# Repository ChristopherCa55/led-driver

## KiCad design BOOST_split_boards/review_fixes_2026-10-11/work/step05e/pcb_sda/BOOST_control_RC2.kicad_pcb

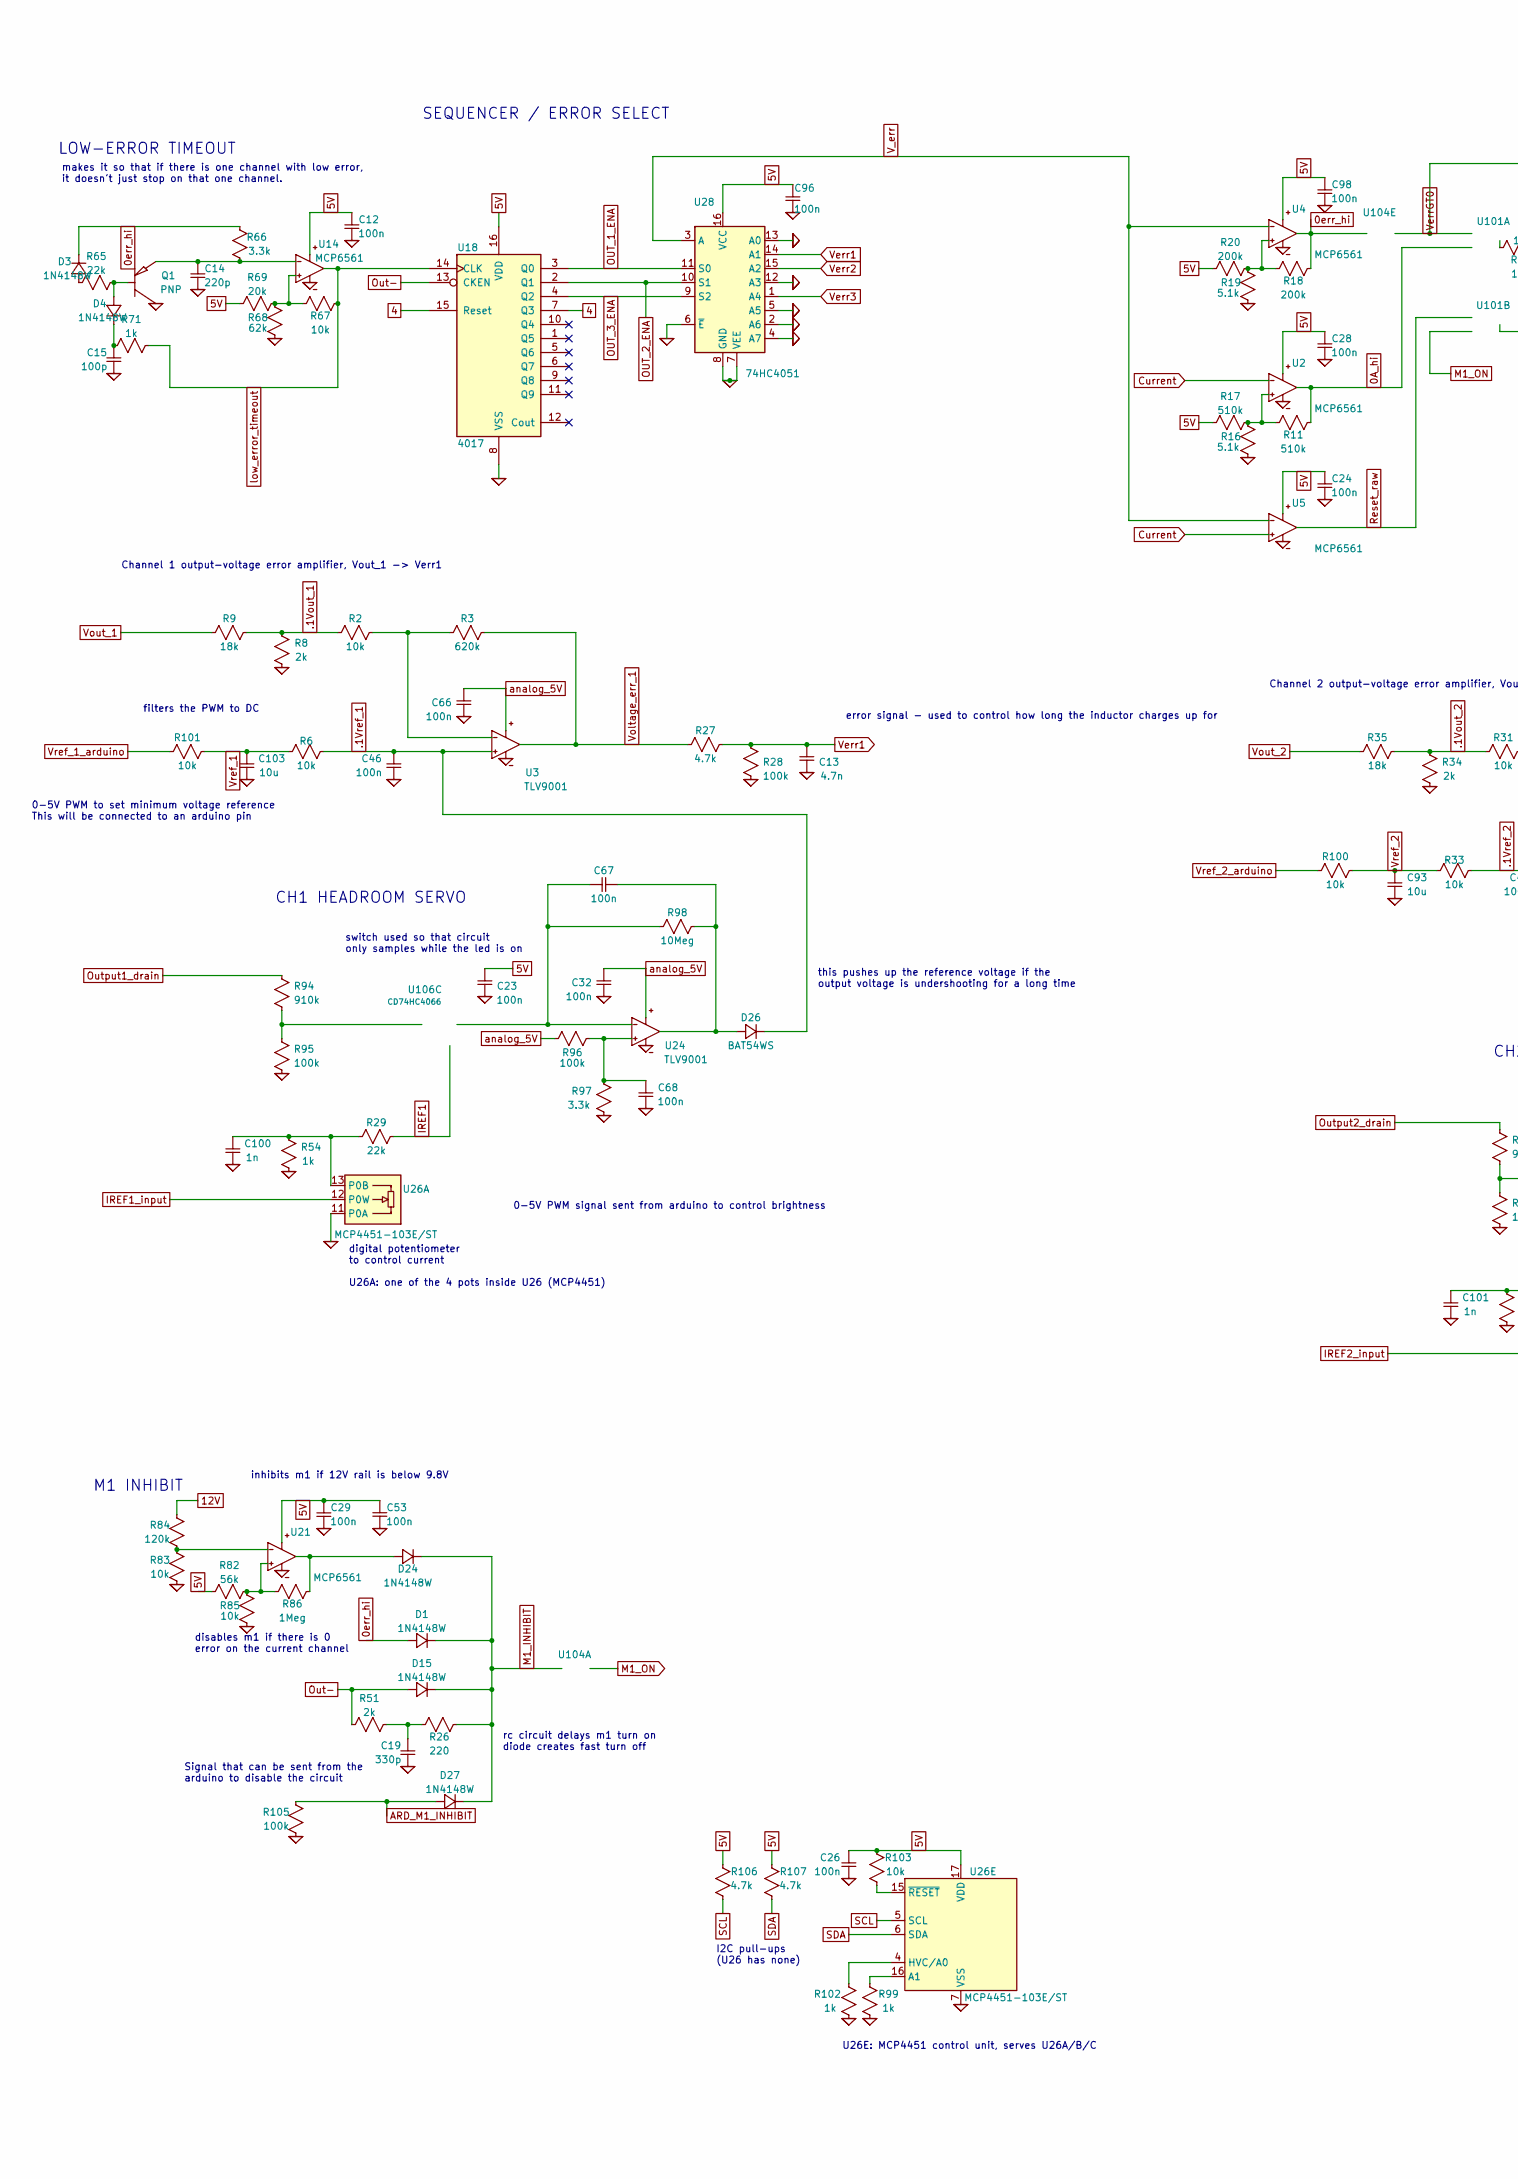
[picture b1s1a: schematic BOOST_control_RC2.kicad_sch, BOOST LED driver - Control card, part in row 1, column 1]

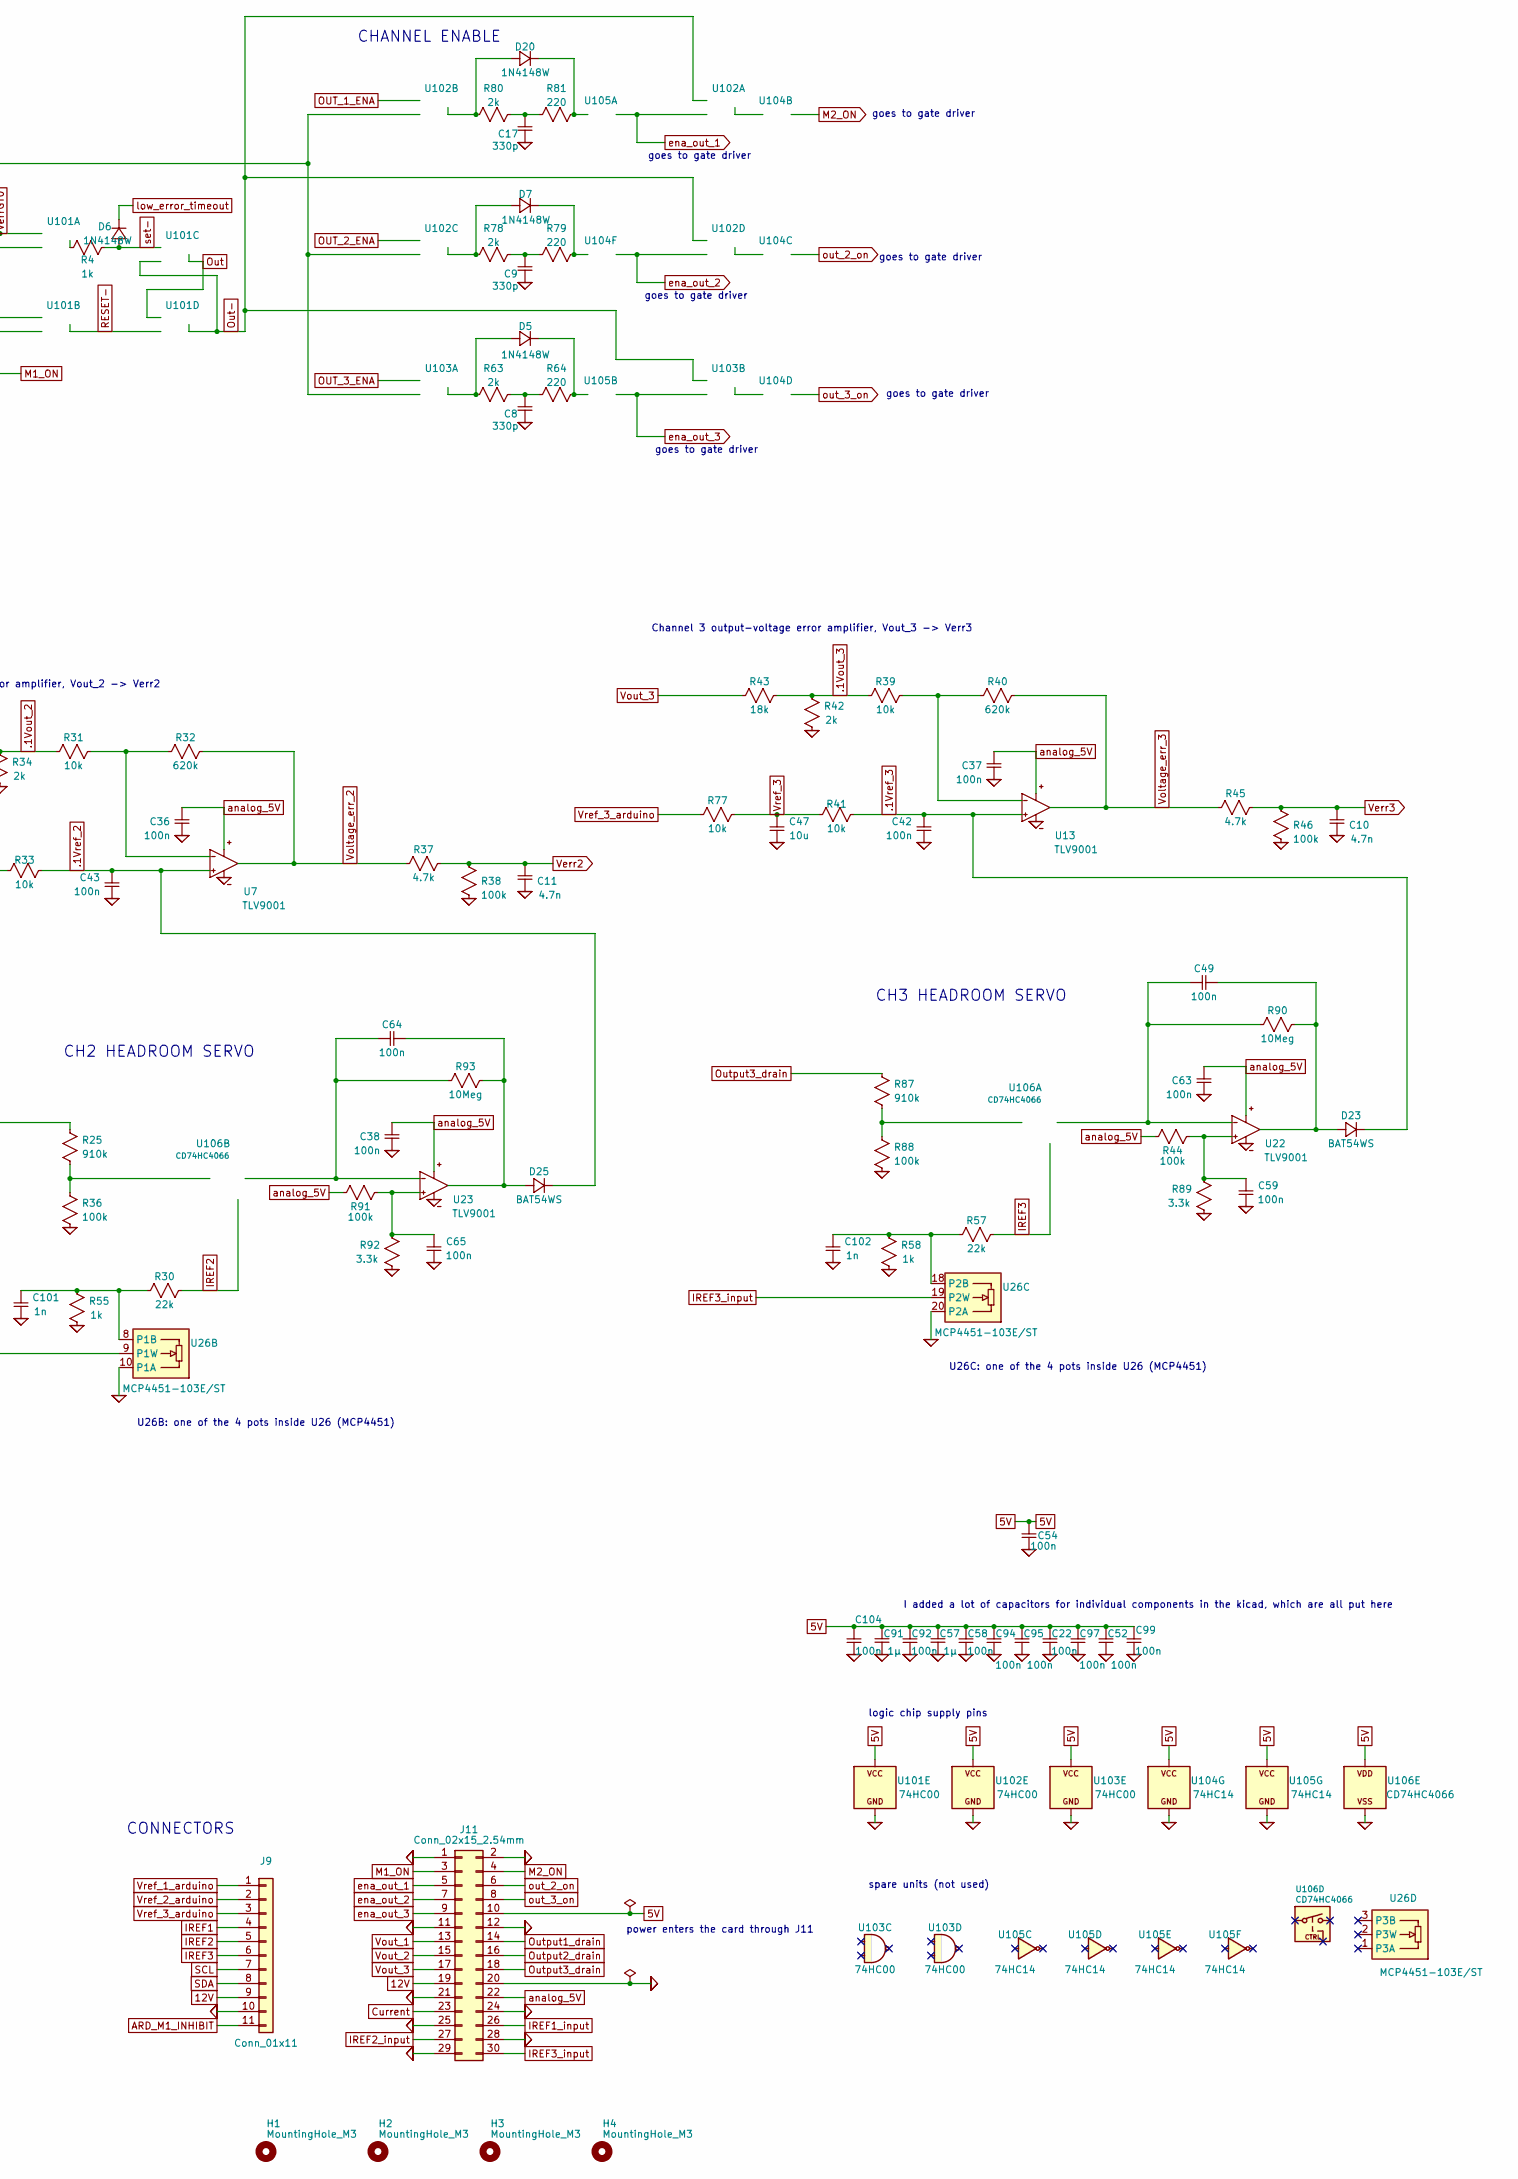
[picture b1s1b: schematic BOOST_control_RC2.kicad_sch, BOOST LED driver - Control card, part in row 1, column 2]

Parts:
C8, C9, C17, C19: 330p; C_0603_1608Metric
C10, C11, C13: 4.7n; C_0603_1608Metric
C12, C22, C23, C24, C26, C28, C29, C32, C36, C37, C38, C42, C43, C46, C52, C53, C54, C58, C59, C63, C65, C66, C68, C92, C94, C95, C96, C97, C98, C99, C104: 100n; C_0603_1608Metric
C14: 220p; C_0603_1608Metric
C15: 100p; C_0603_1608Metric
C47, C93, C103: 10u; C_0603_1608Metric
C49, C64, C67: 100n; C_1206_3216Metric
C57, C91: 1µ; C_0805_2012Metric
C100, C101, C102: 1n; C_0603_1608Metric
D1, D3, D4, D5, D6, D7, D15, D20, D24, D27: 1N4148W; D_SOD-123
D23, D25, D26: BAT54WS; D_SOD-323
H1, H2, H3, H4: MountingHole_M3; MountingHole_3.2mm_M3
J9: Conn_01x11; WirePads_11_Staggered_P1.27mm_Drill1.0mm_TieSlots
J11: Conn_02x15_2.54mm; PinHeader_2x15_P2.54mm_Vertical; MPN TSW-115-07-G-D
Q1: PNP; SOT-23
R2, R6, R31, R33, R39, R41, R67, R77, R83, R85, R100, R101, R103: 10k; R_0603_1608Metric
R3, R32, R40: 620k; R_0603_1608Metric
R4, R54, R55, R58, R71, R99, R102: 1k; R_0603_1608Metric
R8, R34, R42, R51, R63, R78, R80: 2k; R_0603_1608Metric
R9, R35, R43: 18k; R_0805_2012Metric
R11, R17: 510k; R_0603_1608Metric
R16, R19: 5.1k; R_0603_1608Metric
R18, R20: 200k; R_0603_1608Metric
R25, R87, R94: 910k; R_0805_2012Metric
R26, R64, R79, R81: 220; R_0603_1608Metric
R27, R37, R45, R106, R107: 4.7k; R_0603_1608Metric
R28, R36, R38, R44, R46, R88, R91, R95, R96, R105: 100k; R_0603_1608Metric
R29, R30, R57: 22k; R_0805_2012Metric
R65: 22k; R_0603_1608Metric
R66, R89, R92, R97: 3.3k; R_0603_1608Metric
R68: 62k; R_0603_1608Metric
R69: 20k; R_0603_1608Metric
R82: 56k; R_0603_1608Metric
R84: 120k; R_0603_1608Metric
R86: 1Meg; R_0805_2012Metric
R90, R93, R98: 10Meg; R_0603_1608Metric
U2, U4, U5, U14, U21: MCP6561; SOT-23-5
U3, U7, U13, U22, U23, U24: TLV9001; SOT-23-5; MPN TLV9001IDBVR
U18: 4017; SOIC-16_3.9x9.9mm_P1.27mm
U26: MCP4451-103E/ST; TSSOP-20_4.4x6.5mm_P0.65mm; MPN MCP4451-103E/ST; LCSC C145613
U28: 74HC4051; SOIC-16_3.9x9.9mm_P1.27mm
U101, U102, U103: 74HC00; SOIC-14_3.9x8.7mm_P1.27mm
U104, U105: 74HC14; SOIC-14_3.9x8.7mm_P1.27mm
U106: CD74HC4066; SOIC-14_3.9x8.7mm_P1.27mm

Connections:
0A_hi: R11.1, U2.1 (OUT), U101.2 (B)
0err_hi: D1.2 (+), D3.1 (-), R18.1, R66.1, U4.1 (OUT), U104.11 (A)
4: U18.7 (Q3), U18.15 (Reset)
5V: C12.1, C22.1, C23.1, C24.1, C26.1, C28.1, C29.1, C52.1, C53.2, C54.1, C57.2, C58.1, C91.2, C92.1, C94.1, C95.1, C96.1, C97.1, C98.1, C99.1, C104.1, J11.10, R17.2, R20.2, R69.2, R82.1, R103.1, R106.1, R107.1, U2.5 (V+), U4.5 (V+), U5.5 (V+), U14.5 (V+), U18.16 (VDD), U21.5 (V+), U26.17 (VDD), U28.16 (VCC), U101.14 (VCC), U102.14 (VCC), U103.14 (VCC), U104.14 (VCC), U105.14 (VCC), U106.14 (VDD)
12V: J9.9, J11.19, R84.1
.1Vout_1: R2.2, R8.1, R9.1
.1Vout_2: R31.2, R34.1, R35.1
.1Vout_3: R39.2, R42.1, R43.1
.1Vref_1: C46.1, D26.1 (-), R6.2, U3.3 (In+)
.1Vref_2: C43.1, D25.1 (-), R33.2, U7.3 (In+)
.1Vref_3: C42.1, D23.1 (-), R41.2, U13.3 (In+)
ARD_M1_INHIBIT: D27.2 (+), J9.11, R105.1
Current: J11.23, U2.4 (In-), U5.3 (In+)
GND: C8.1, C9.1, C10.1, C11.1, C12.2, C13.1, C14.2, C15.2, C17.1, C19.2, C22.2, C23.2, C24.2, C26.2, C28.2, C29.2, C32.2, C36.1, C37.1, C38.1, C42.2, C43.2, C46.2, C47.2, C52.2, C53.1, C54.2, C57.1, C58.2, C59.2, C63.2, C65.2, C66.2, C68.2, C91.1, C92.2, C93.2, C94.2, C95.2, C96.2, C97.2, C98.2, C99.2, C100.2, C101.2, C102.2, C103.2, C104.2, J9.10, J11.1, J11.2, J11.11, J11.12, J11.20, J11.21, J11.24, J11.25, J11.28, J11.29, Q1.3 (C), R8.2, R16.2, R19.2, R28.1, R34.2, R36.2, R38.1, R42.2, R46.1, R54.2, R55.2, R58.2, R68.2, R83.2, R85.2, R88.2, R89.2, R92.2, R95.2, R97.2, R99.2, R102.2, R105.2, U2.2 (V-), U3.2 (V-), U4.2 (V-), U5.2 (V-), U7.2 (V-), U13.2 (V-), U14.2 (V-), U18.8 (VSS), U21.2 (V-), U22.2 (V-), U23.2 (V-), U24.2 (V-), U26.7 (VSS), U26.10 (P1A), U26.11 (P0A), U26.20 (P2A), U28.2 (A6), U28.4 (A7), U28.5 (A5), U28.6 (~E), U28.7 (VEE), U28.8 (GND), U28.12 (A3), U28.13 (A0), U101.7 (GND), U102.7 (GND), U103.7 (GND), U104.7 (GND), U105.7 (GND), U106.7 (VSS)
IREF1: J9.4, R29.1, U106.6 (CTRL)
IREF1_input: J11.26, U26.12 (P0W)
IREF2: J9.5, R30.1, U106.5 (CTRL)
IREF2_input: J11.27, U26.9 (P1W)
IREF3: J9.6, R57.1, U106.13 (CTRL)
IREF3_input: J11.30, U26.19 (P2W)
M1_INHIBIT: D1.1 (-), D15.1 (-), D24.1 (-), D27.1 (-), R26.1, U104.1 (A)
M1_ON: J11.3, U101.5 (B), U104.2 (Y)
M2_ON: J11.4, U104.4 (Y)
unnamed: C8.2, R63.1, R64.1
unnamed: C9.2, R78.1, R79.1
unnamed: C17.2, R80.1, R81.1
unnamed: C19.1, R26.2, R51.2
unnamed: D3.2 (+), R65.2
unnamed: D4.2 (+), Q1.1 (B), R65.1
unnamed: C15.1, D4.1 (-), R71.1
unnamed: D5.2 (+), R63.2, U103.3 (Y)
unnamed: D5.1 (-), R64.2, U105.3 (A)
unnamed: D7.2 (+), R78.2, U102.8 (Y)
unnamed: D7.1 (-), R79.2, U104.13 (A)
unnamed: D20.2 (+), R80.2, U102.6 (Y)
unnamed: D20.1 (-), R81.2, U105.1 (A)
unnamed: C49.2, D23.2 (+), R90.2, U22.1 (OUT)
unnamed: D24.2 (+), R86.1, U21.1 (OUT)
unnamed: C64.2, D25.2 (+), R93.2, U23.1 (OUT)
unnamed: C67.2, D26.2 (+), R98.2, U24.1 (OUT)
unnamed: C14.1, Q1.2 (E), R66.2, U14.4 (In-)
unnamed: R11.2, R16.1, R17.1, U2.3 (In+)
unnamed: R2.1, R3.2, U3.4 (In-)
unnamed: R18.2, R19.1, R20.1, U4.3 (In+)
unnamed: R31.1, R32.2, U7.4 (In-)
unnamed: R39.1, R40.2, U13.4 (In-)
unnamed: R67.2, R68.1, R69.1, U14.3 (In+)
unnamed: R82.2, R85.1, R86.2, U21.3 (In+)
unnamed: R83.1, R84.2, U21.4 (In-)
unnamed: C59.1, R44.2, R89.1, U22.3 (In+)
unnamed: C65.1, R91.2, R92.1, U23.3 (In+)
unnamed: C68.1, R96.2, R97.1, U24.3 (In+)
unnamed: C100.1, R29.2, R54.1, U26.13 (P0B)
unnamed: C101.1, R30.2, R55.1, U26.8 (P1B)
unnamed: C102.1, R57.2, R58.1, U26.18 (P2B)
unnamed: R99.1, U26.16 (A1)
unnamed: R102.1, U26.4 (HVC/A0)
unnamed: R103.2, U26.15 (~RESET)
unnamed: R4.2, U101.3 (Y)
unnamed: U102.3 (Y), U104.3 (A)
unnamed: U102.11 (Y), U104.5 (A)
unnamed: U103.6 (Y), U104.9 (A)
unnamed: R87.2, R88.1, U106.1 (A)
unnamed: C49.1, R90.1, U22.4 (In-), U106.2 (B)
unnamed: R25.2, R36.1, U106.3 (A)
unnamed: C64.1, R93.1, U23.4 (In-), U106.4 (B)
unnamed: R94.2, R95.1, U106.8 (A)
unnamed: C67.1, R98.1, U24.4 (In-), U106.9 (B)
OUT_1_ENA: U18.3 (Q0), U28.11 (S0), U102.4 (A)
OUT_2_ENA: U18.2 (Q1), U28.10 (S1), U102.10 (A)
OUT_3_ENA: U18.4 (Q2), U28.9 (S2), U103.1 (A)
Out: U101.8 (Y), U101.13 (A)
Out-: D15.2 (+), R51.1, U18.13 (CKEN), U101.9 (B), U101.11 (Y), U102.1 (A), U102.13 (A), U103.5 (B)
Output1_drain: J11.14, R94.1
Output2_drain: J11.16, R25.1
Output3_drain: J11.18, R87.1
RESET-: U101.6 (Y), U101.12 (B)
Reset_raw: U5.1 (OUT), U101.4 (A)
SCL: J9.7, R106.2, U26.5 (SCL)
SDA: J9.8, R107.2, U26.6 (SDA)
V_err: U4.4 (In-), U5.4 (In-), U28.3 (A)
Verr1: C13.2, R27.2, R28.2, U28.14 (A1)
Verr2: C11.2, R37.2, R38.2, U28.15 (A2)
Verr3: C10.2, R45.2, R46.2, U28.1 (A4)
VerrGT0: U101.1 (A), U102.5 (B), U102.9 (B), U103.2 (B), U104.10 (Y)
Voltage_err_1: R3.1, R27.1, U3.1 (OUT)
Voltage_err_2: R32.1, R37.1, U7.1 (OUT)
Voltage_err_3: R40.1, R45.1, U13.1 (OUT)
Vout_1: J11.13, R9.2
Vout_2: J11.15, R35.2
Vout_3: J11.17, R43.2
Vref_1: C103.1, R6.1, R101.2
Vref_1_arduino: J9.1, R101.1
Vref_2: C93.1, R33.1, R100.2
Vref_2_arduino: J9.2, R100.1
Vref_3: C47.1, R41.1, R77.2
Vref_3_arduino: J9.3, R77.1
analog_5V: C32.1, C36.2, C37.2, C38.2, C63.1, C66.1, J11.22, R44.1, R91.1, R96.1, U3.5 (V+), U7.5 (V+), U13.5 (V+), U22.5 (V+), U23.5 (V+), U24.5 (V+)
ena_out_1: J11.5, U102.2 (B), U105.2 (Y)
ena_out_2: J11.7, U102.12 (B), U104.12 (Y)
ena_out_3: J11.9, U103.4 (A), U105.4 (Y)
low_error_timeout: D6.1 (-), R67.1, R71.2, U14.1 (OUT), U18.14 (CLK)
out_2_on: J11.6, U104.6 (Y)
out_3_on: J11.8, U104.8 (Y)
set-: D6.2 (+), R4.1, U101.10 (A)

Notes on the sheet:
M1 INHIBIT
disables m1 if there is 0 error on the current channel
goes to gate driver
CONNECTORS
U26B: one of the 4 pots inside U26 (MCP4451)
U26A: one of the 4 pots inside U26 (MCP4451)
switch used so that circuit only samples while the led is on
0-5V PWM to set minimum voltage reference This will be connected to an arduino pin
U26C: one of the 4 pots inside U26 (MCP4451)
spare units (not used)
this pushes up the reference voltage if the output voltage is undershooting for a long time
LOW-ERROR TIMEOUT
0-5V PWM signal sent from arduino to control brightness
Channel 2 output-voltage error amplifier, Vout_2 -> Verr2
logic chip supply pins
power enters the card through J11
Signal that can be sent from the arduino to disable the circuit
CH3 HEADROOM SERVO
rc circuit delays m1 turn on diode creates fast turn off
inhibits m1 if 12V rail is below 9.8V
CH1 HEADROOM SERVO
filters the PWM to DC
CH2 HEADROOM SERVO
I added a lot of capacitors for individual components in the kicad, which are all put here
U26E: MCP4451 control unit, serves U26A/B/C
digital potentiometer to control current
Channel 1 output-voltage error amplifier, Vout_1 -> Verr1
SEQUENCER / ERROR SELECT
error signal - used to control how long the inductor charges up for
Channel 3 output-voltage error amplifier, Vout_3 -> Verr3
CHANNEL ENABLE
makes it so that if there is one channel with low error, it doesn't just stop on that one channel.
I2C pull-ups (U26 has none)

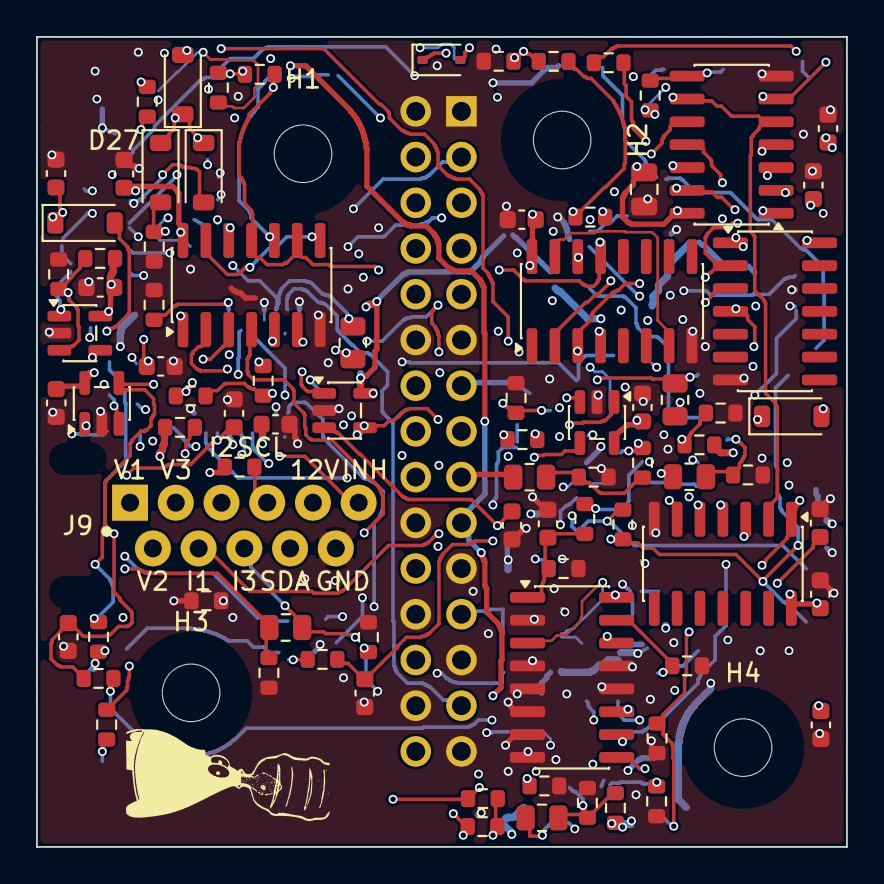
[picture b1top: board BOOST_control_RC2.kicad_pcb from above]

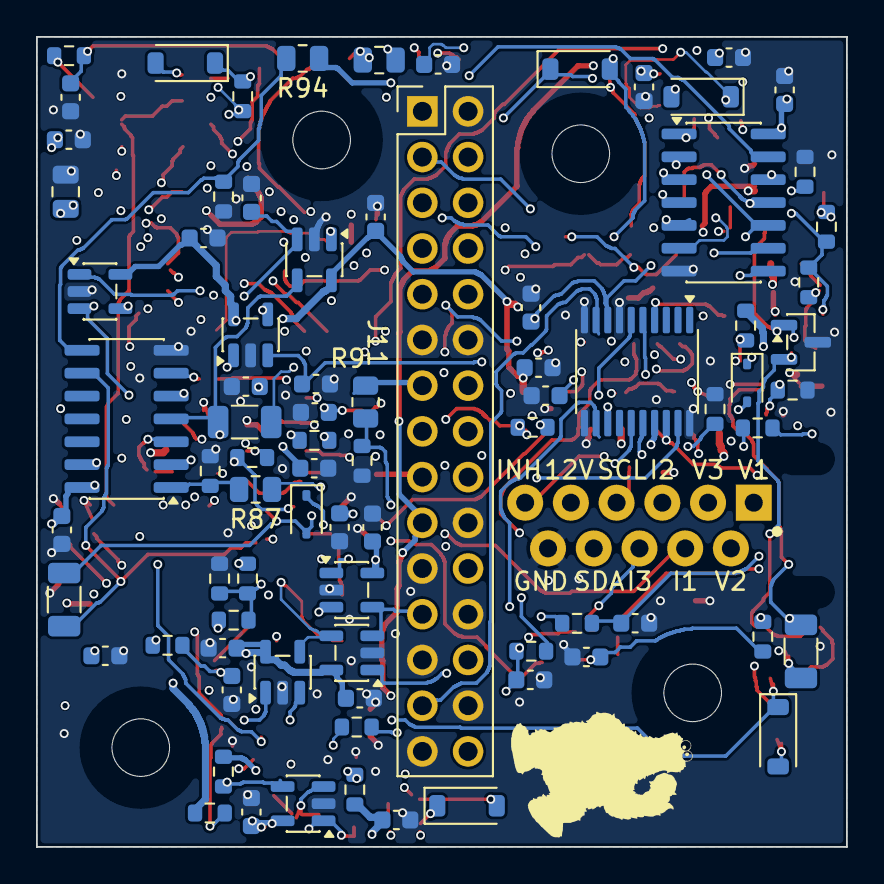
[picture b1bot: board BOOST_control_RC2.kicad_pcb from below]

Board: 6 copper layers, 45.0 x 45.0 mm, 168 parts (81 on the bottom side), 105 nets.
